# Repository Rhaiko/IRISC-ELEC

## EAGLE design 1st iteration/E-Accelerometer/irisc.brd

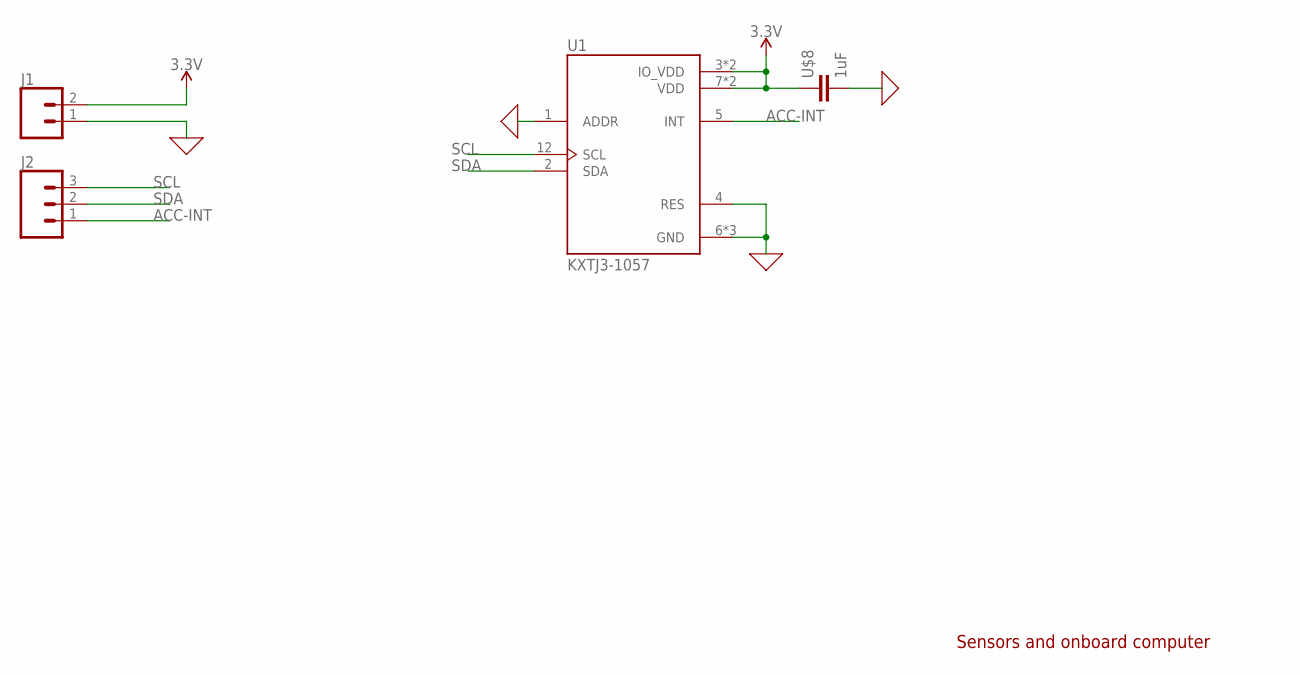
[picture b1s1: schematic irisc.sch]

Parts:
J1: CONN_02; 1X02
J2: CONN_03; 1X03
U1: KXTJ3-1057; KIONIX_KXTJ3-1057
U$8: 1uF; RESC0603_N

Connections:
0: J1.1, U1.1 (ADDR), U1.4 (RES), U1.6 (GND), U1.8 (GND), U1.9 (GND), U$8.2
3.3V: J1.2, U1.3 (IO_VDD), U1.7 (VDD), U1.10 (VDD), U1.11 (IO_VDD), U$8.1
ACC-INT: J2.1, U1.5 (INT)
SCL: J2.3, U1.12 (SCL)
SDA: J2.2, U1.2 (SDA)

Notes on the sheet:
Sensors and onboard computer

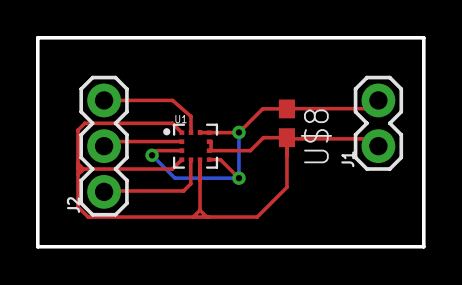
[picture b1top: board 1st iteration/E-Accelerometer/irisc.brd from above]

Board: 2 copper layers, 21.4 x 11.6 mm, 4 parts (0 on the bottom side), 5 nets.

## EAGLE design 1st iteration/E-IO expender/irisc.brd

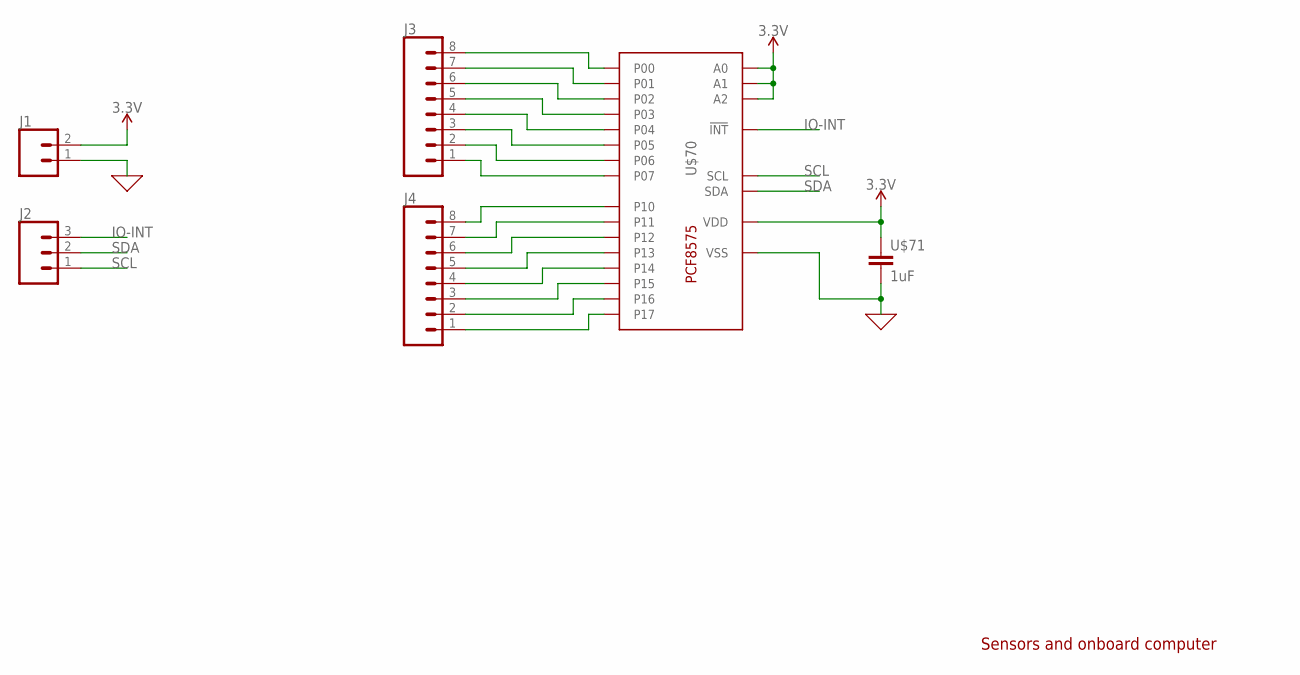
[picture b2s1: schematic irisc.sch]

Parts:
J1: CONN_02; 1X02
J2: CONN_03; 1X03
J3, J4: CONN_08"; 1X08
U$70: PCF8575CSSOP24N; SOP65P810X120-24
U$71: 1uF; RESC0603_N

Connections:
0: J1.1, U$70.12 (VSS), U$71.2
3.3V: J1.2, U$70.2 (A1), U$70.3 (A2), U$70.21 (A0), U$70.24 (VDD), U$71.1
IO-INT: J2.3, U$70.1 (!INT)
unnamed: J3.8, U$70.4 (P00)
unnamed: J3.7, U$70.5 (P01)
unnamed: J3.6, U$70.6 (P02)
unnamed: J3.5, U$70.7 (P03)
unnamed: J3.4, U$70.8 (P04)
unnamed: J3.3, U$70.9 (P05)
unnamed: J3.2, U$70.10 (P06)
unnamed: J3.1, U$70.11 (P07)
unnamed: J4.8, U$70.13 (P10)
unnamed: J4.7, U$70.14 (P11)
unnamed: J4.6, U$70.15 (P12)
unnamed: J4.5, U$70.16 (P13)
unnamed: J4.4, U$70.17 (P14)
unnamed: J4.3, U$70.18 (P15)
unnamed: J4.2, U$70.19 (P16)
unnamed: J4.1, U$70.20 (P17)
SCL: J2.1, U$70.22 (SCL)
SDA: J2.2, U$70.23 (SDA)

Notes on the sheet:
Sensors and onboard computer

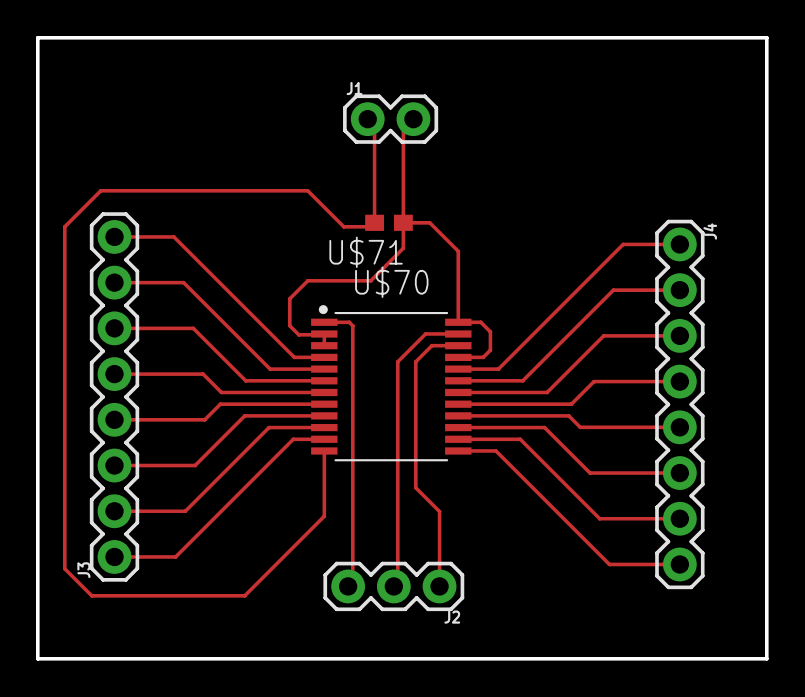
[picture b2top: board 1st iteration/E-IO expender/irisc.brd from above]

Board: 2 copper layers, 40.5 x 34.5 mm, 6 parts (0 on the bottom side), 21 nets.

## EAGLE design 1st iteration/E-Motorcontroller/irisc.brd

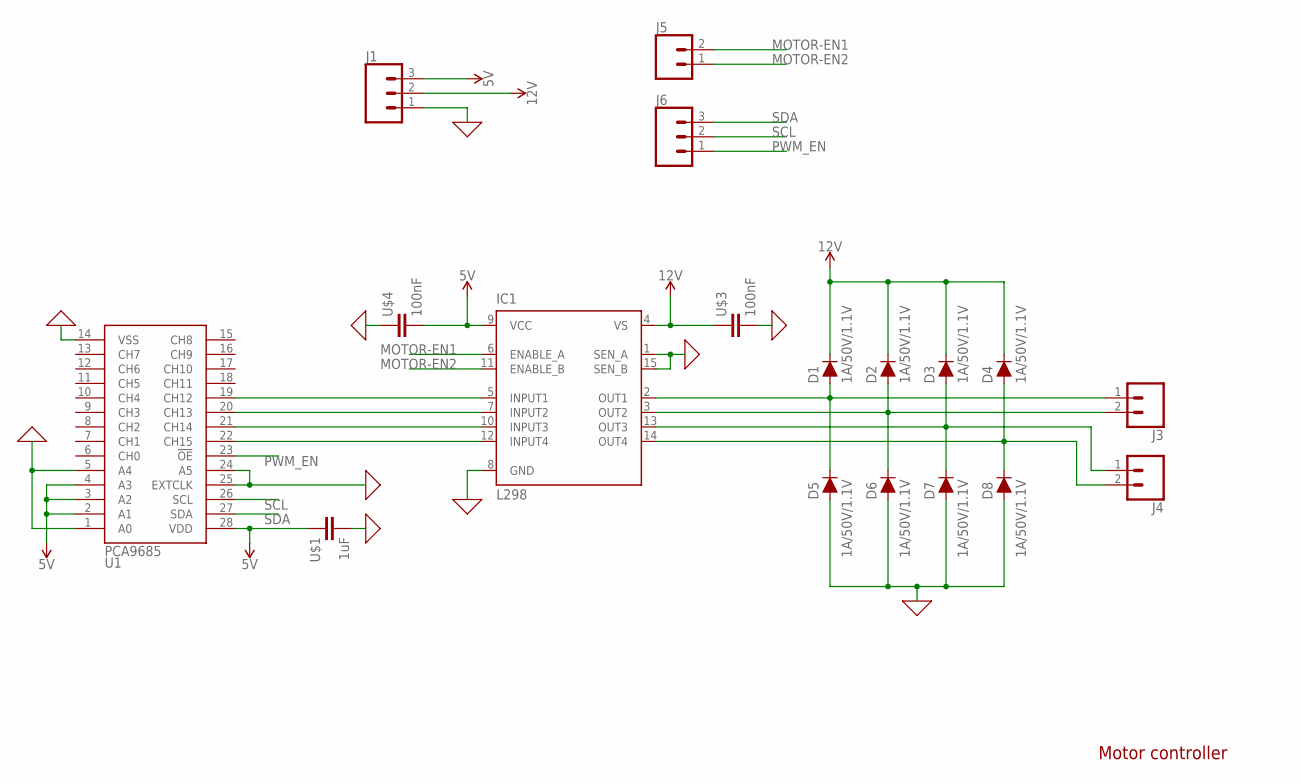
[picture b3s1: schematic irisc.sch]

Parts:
D1, D2, D3, D4, D5, D6, D7, D8: 1A/50V/1.1V; DIODE-1N4001
IC1: L298; MULTIWATT-15
J1, J6: CONN_03; 1X03
J3, J4: CONN_023.5MM; SCREWTERMINAL-3.5MM-2
J5: CONN_02; 1X02
U1: PCA9685; TSSOP-28_4MM
U$1: 1uF; RESC0805_L
U$3, U$4: 100nF; RESC0603_L

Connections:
0: D5.A, D6.A, D7.A, D8.A, IC1.1 (SEN_A), IC1.8 (GND), IC1.15 (SEN_B), J1.1, U1.1 (A0), U1.5 (A4), U1.14 (VSS), U1.24 (A5), U1.25 (EXTCLK), U$1.2, U$3.2, U$4.1
5V: IC1.9 (VCC), J1.3, U1.2 (A1), U1.3 (A2), U1.4 (A3), U1.28 (VDD), U$1.1, U$4.2
12V: D1.C, D2.C, D3.C, D4.C, IC1.4 (VS), J1.2, U$3.1
MOTOR-EN1: IC1.6 (ENABLE_A), J5.2
MOTOR-EN2: IC1.11 (ENABLE_B), J5.1
unnamed: IC1.5 (INPUT1), U1.19 (CH12)
unnamed: IC1.7 (INPUT2), U1.20 (CH13)
unnamed: IC1.10 (INPUT3), U1.21 (CH14)
unnamed: IC1.12 (INPUT4), U1.22 (CH15)
unnamed: D1.A, D5.C, IC1.2 (OUT1), J3.1
unnamed: D2.A, D6.C, IC1.3 (OUT2), J3.2
unnamed: D3.A, D7.C, IC1.13 (OUT3), J4.1
unnamed: D4.A, D8.C, IC1.14 (OUT4), J4.2
PWM_EN: J6.1, U1.23 (!OE)
SCL: J6.2, U1.26 (SCL)
SDA: J6.3, U1.27 (SDA)

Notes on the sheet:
Motor controller

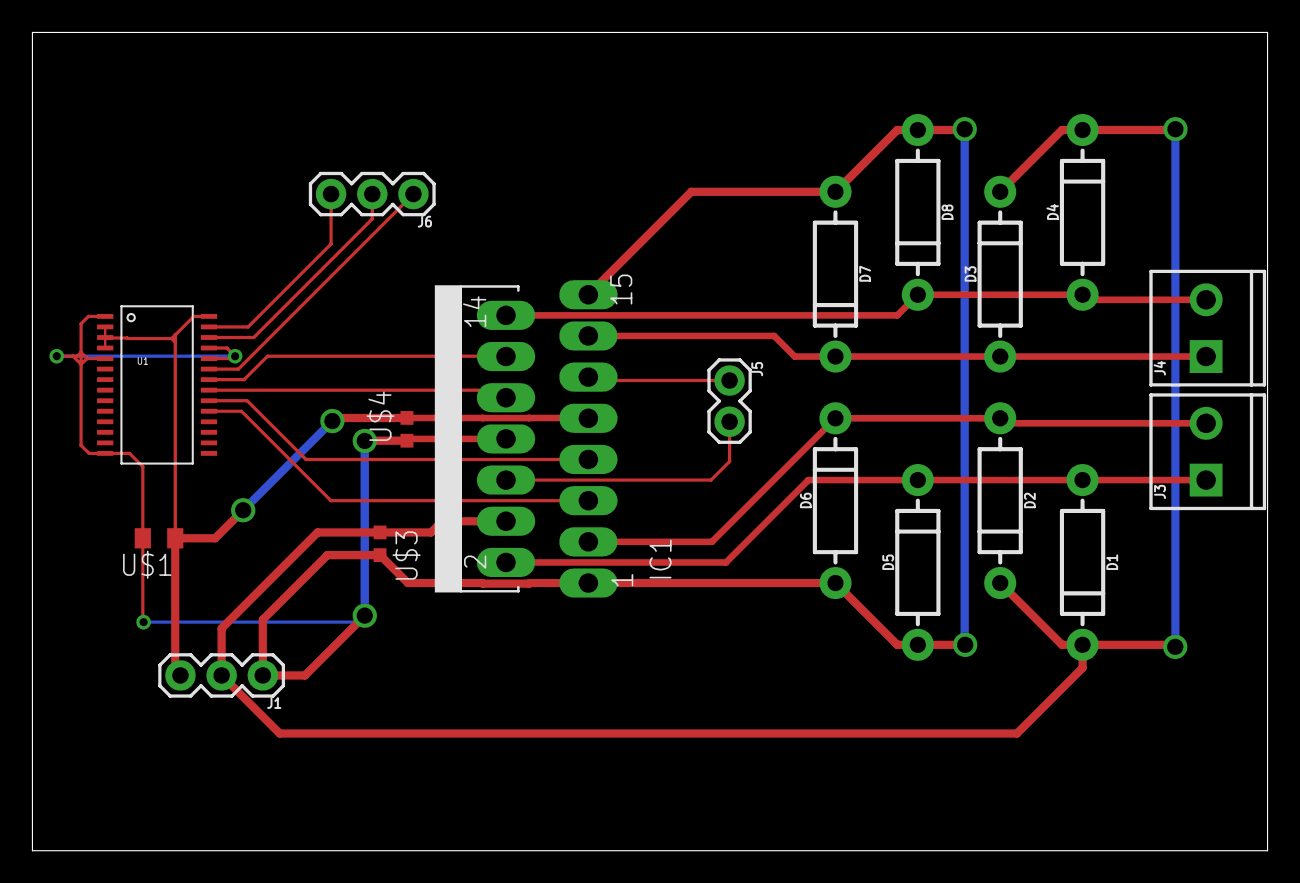
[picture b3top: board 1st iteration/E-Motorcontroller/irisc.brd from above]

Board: 2 copper layers, 76.2 x 50.5 mm, 18 parts (0 on the bottom side), 16 nets.

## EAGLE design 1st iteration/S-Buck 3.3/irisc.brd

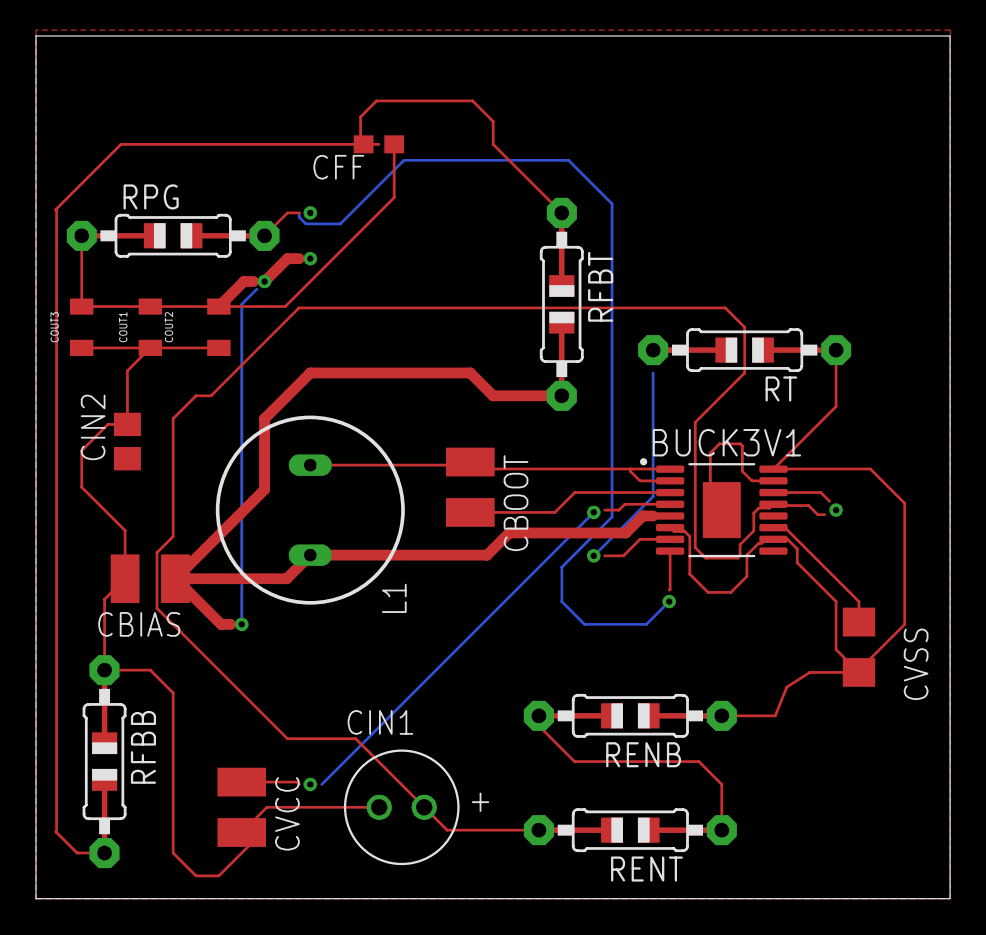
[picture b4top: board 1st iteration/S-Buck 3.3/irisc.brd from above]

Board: 2 copper layers, 50.8 x 47.9 mm, 18 parts (0 on the bottom side), 13 nets.

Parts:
BUCK3V1: SOP65P640X120-17N
CBIAS: 1 uF; C1210
CBOOT: 0.47 uF; C1210
CFF: 44pF; C0603
CIN1: 0.1uF; 6.3X2.5X0.9(DXAXB)
CIN2: 10uF; C0805
COUT1, COUT2, COUT3: 6 uF; WCAP-CSGP_0805_WAVE
CVCC: 2.2 uF; C1210
CVSS: 22nF; C1206
L1: BS11
RENB: 1 M; 0805-THM
RENT: 1 M; 0805-THM
RFBB: 442 k; 0805-THM
RFBT: 1 M; 0805-THM
RPG: 10 k; 0805-THM
RT: 200 k; 0805-THM

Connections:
3.3V: BUCK3V1.5, CBIAS.1, CFF.1, COUT1.2, COUT2.2, COUT3.2, L1.2, RFBT.2, RPG.1
GND: CBIAS.2, CIN1.2, CIN2.2, COUT1.1, COUT2.1, COUT3.1, CVCC.2, RFBB.1
unnamed: BUCK3V1.1, BUCK3V1.2, CBOOT.1, L1.1
unnamed: BUCK3V1.7, RT.2
unnamed: BUCK3V1.11, CVSS.1
unnamed: BUCK3V1.3, CBOOT.2
unnamed: BUCK3V1.4, CVCC.1
unnamed: CFF.2, RFBB.2, RFBT.1
unnamed: BUCK3V1.8, RPG.2
unnamed: RENB.2, RENT.1
PGND1: BUCK3V1.15, BUCK3V1.17
PGND2: BUCK3V1.6, BUCK3V1.10, BUCK3V1.16, CVSS.2, RENB.1, RT.1
VCC: BUCK3V1.13, BUCK3V1.14, CIN1.1, CIN2.1, RENT.2

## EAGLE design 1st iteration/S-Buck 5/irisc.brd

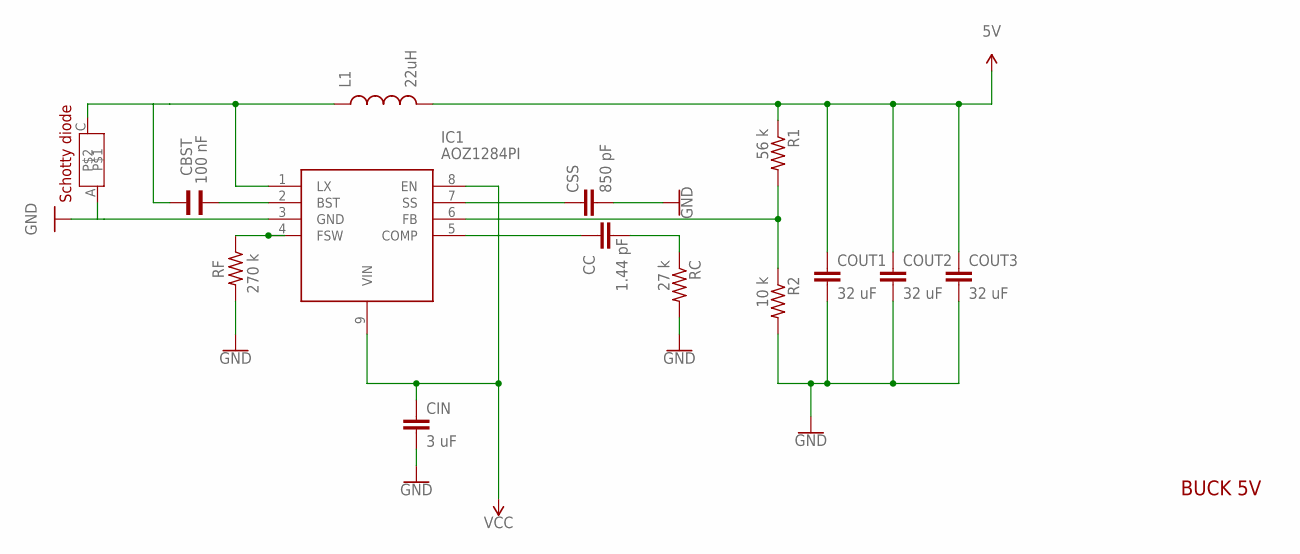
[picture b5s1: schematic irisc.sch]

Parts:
CBST: 100 nF; WCAP-CSGP_0805_WAVE
CC: 1.44 pF; C1206
CIN: 3 uF; C1210
COUT1, COUT2, COUT3: 32 uF; C1812
CSS: 850 pF; C0805
IC1: AOZ1284PI; SOIC127P600X170-9N
L1: 22uH; L0603
R1: 56 k; 0805-THM
R2: 10 k; 0805-THM
RC: 27 k; 0805-THM
RF: 270 k; 0805-THM
U$1: SCHOTTY-DIODE-IRISC; DO-214AC

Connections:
5V: COUT1.1, COUT2.1, COUT3.1, L1.2, R1.1
GND: CIN.2, COUT1.2, COUT2.2, COUT3.2, CSS.2, IC1.3 (GND), R2.2, RC.2, RF.2, U$1.A
unnamed: IC1.4 (FSW), RF.1
unnamed: CBST.2, IC1.2 (BST)
unnamed: CBST.1, IC1.1 (LX), L1.1, U$1.C
unnamed: CC.1, IC1.5 (COMP)
unnamed: CSS.1, IC1.7 (SS)
unnamed: IC1.6 (FB), R1.2, R2.1
unnamed: CC.2, RC.1
VCC: CIN.1, IC1.8 (EN), IC1.9 (VIN)

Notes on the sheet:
BUCK 5V

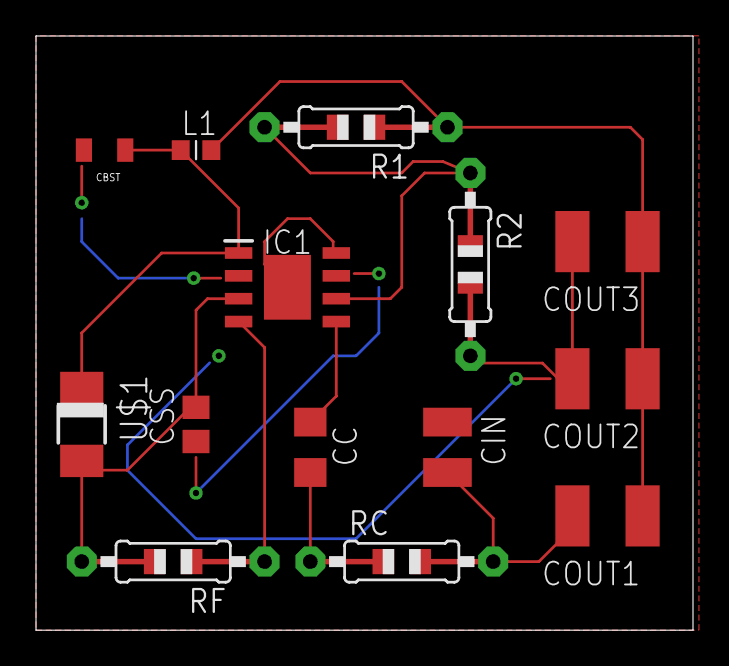
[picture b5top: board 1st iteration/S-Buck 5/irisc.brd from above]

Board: 2 copper layers, 36.5 x 33.0 mm, 14 parts (0 on the bottom side), 10 nets.

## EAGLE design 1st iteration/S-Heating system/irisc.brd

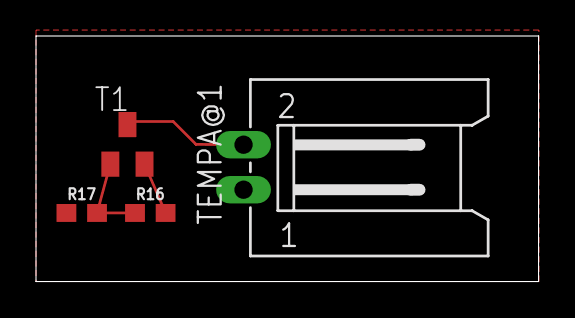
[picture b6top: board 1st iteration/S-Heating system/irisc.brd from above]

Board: 2 copper layers, 27.9 x 13.6 mm, 4 parts (0 on the bottom side), 3 nets.

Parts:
R16: 100k; 0603
R17: 10k; 0603
T1: SOT23-BEC
TEMPA@1: L02P

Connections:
5V: R16.2, T1.E
unnamed: R16.1, R17.2, T1.B
unnamed: T1.C, TEMPA@1.2

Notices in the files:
parts and their libraries:
SparkFun-Connectors: Licensing: Creative Commons ShareAlike 4.0 International - https://creativecommons.org/licenses/by-sa/4.0
Wurth_Elektronik_Electromechanic_Coaxial: Copyright: Würth Elektronik
